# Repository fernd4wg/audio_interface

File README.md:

# Audio Interface

## Important Note
Make sure to always **git pull** before you start working.

This is being made on KiCAD 10. If you are using a different version and wish to make contributions there may be problems.

## Getting Started
To get this project on your computer, ensure you have git installed on your computer and in your terminal run:
```
git clone https://github.com/fernd4wg/audio_interface
```

After that, open up the *audio_interface.kicad_pro* file through KiCAD.

Done.

## 3D Models
I am going to use 3rd party 3D models for this project because KiCAD does not have all the necessary 3D models for this PCB.

I will provide a fork of my KiCAD 3D model directory that you can replace with yours if you so wish.

Additionally, I will provide a folder with the 3rd party 3D models I use for this project in this repository. ***Note** that those being here will not make them appear on the 3D model of the PCB. You will need to set that up yourself if you do not replace your KiCAD 3D model library with mine*

## Technical Details
If you are curious about the technical details of the audio interface I will eventually provide a documentation folder where a there will be a document that documents the technical side of the design.

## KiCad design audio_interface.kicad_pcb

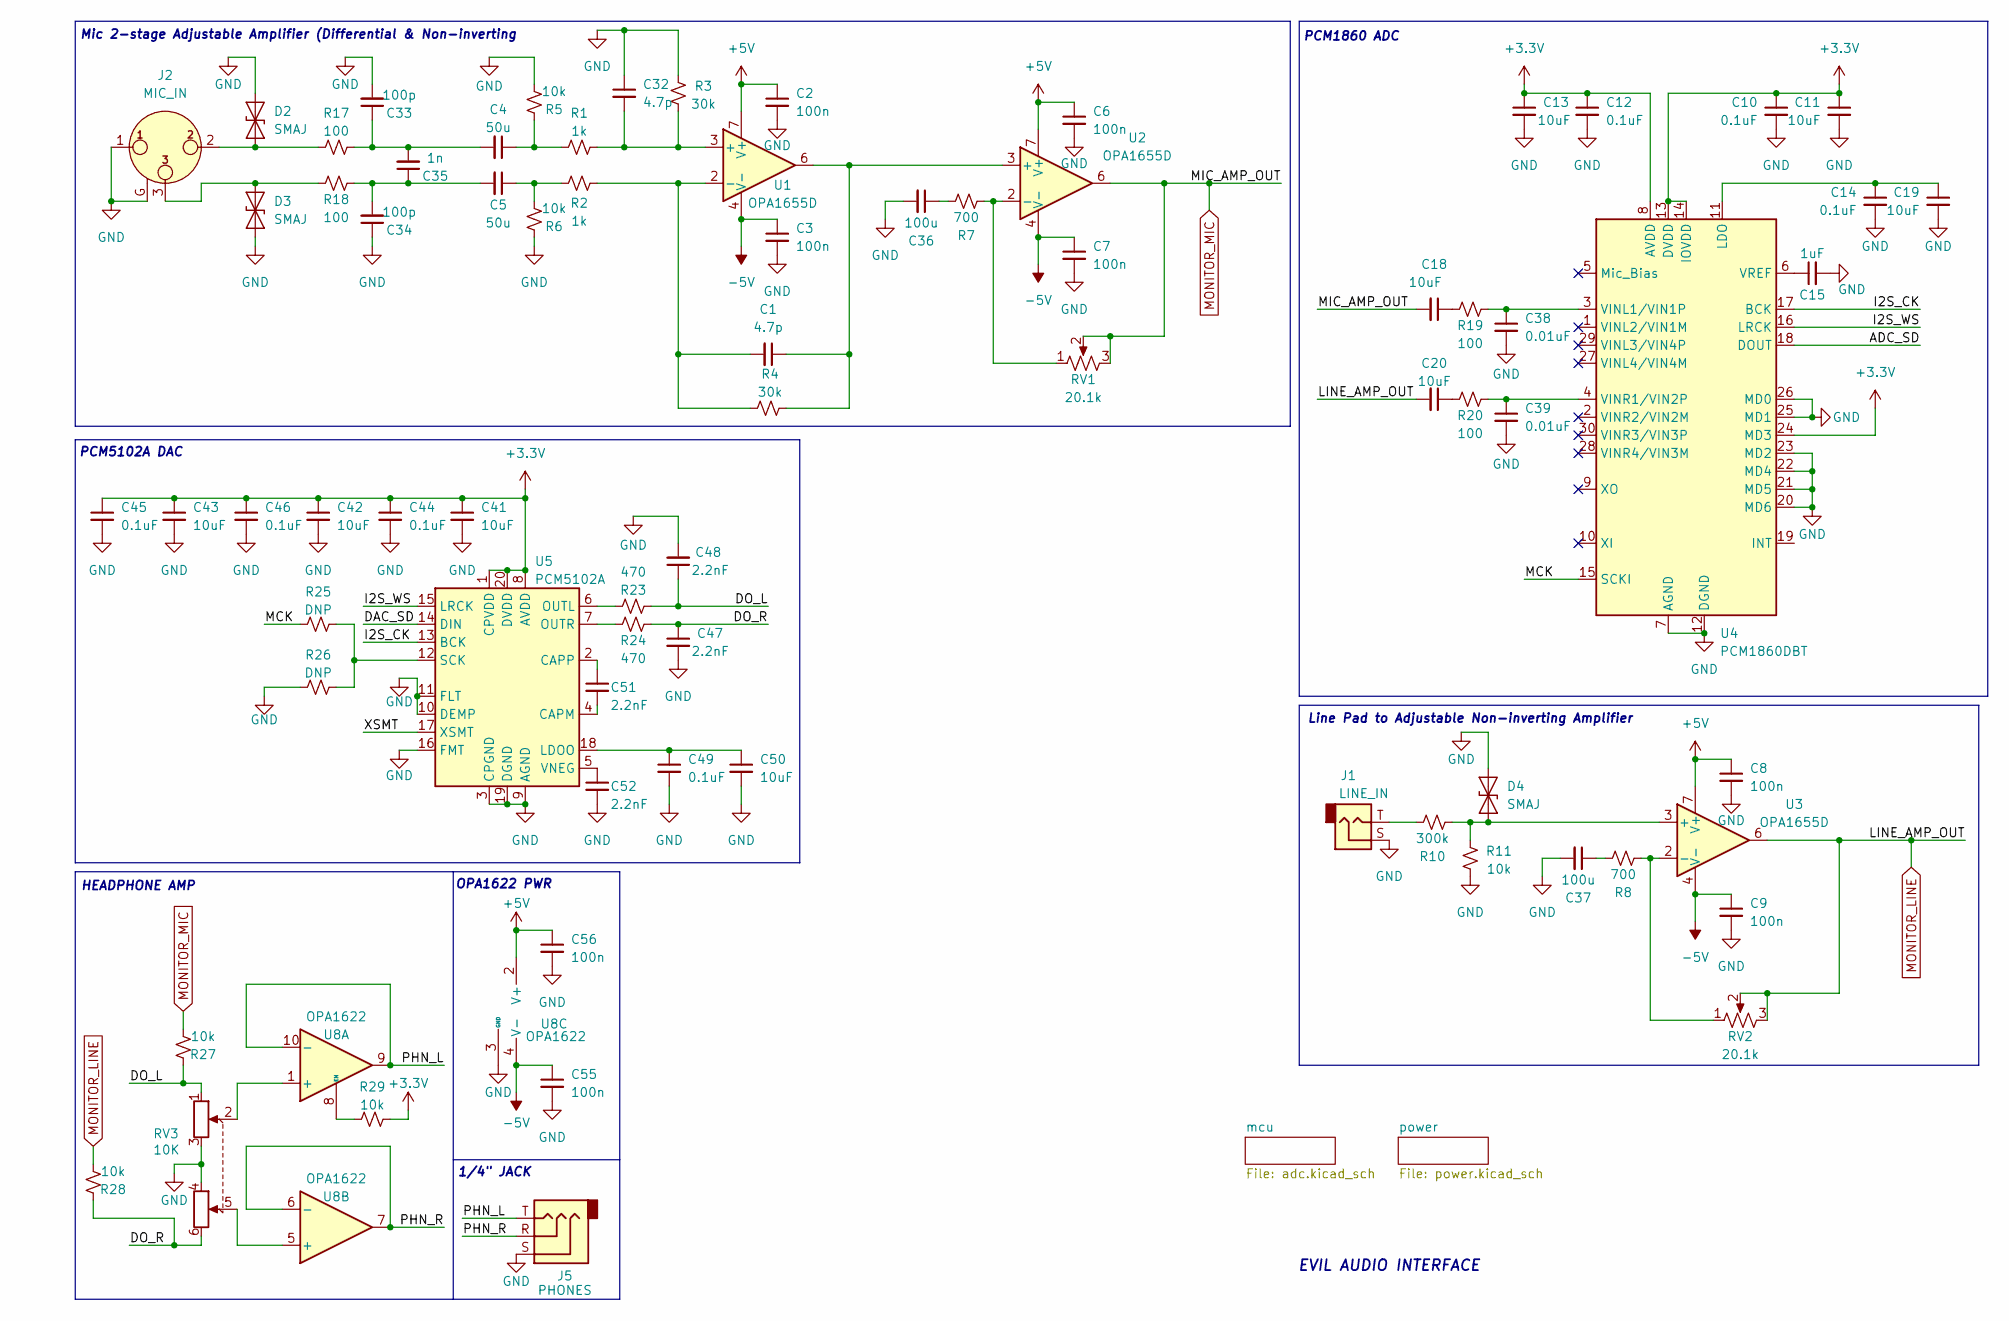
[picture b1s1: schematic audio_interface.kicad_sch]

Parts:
C1, C32: 4.7p; C_0805_2012Metric
C2, C3, C6, C7, C8, C9, C55, C56: 100n; C_0805_2012Metric
C4, C5: 50u; C_0805_2012Metric
C10, C12, C14, C44, C45, C46, C49: 0.1uF; C_0805_2012Metric
C11, C13, C18, C19, C20, C41, C42, C43, C50: 10uF; C_0805_2012Metric
C15: 1uF; C_0805_2012Metric
C33, C34: 100p; C_0805_2012Metric
C35: 1n; C_0805_2012Metric
C36, C37: 100u; C_0805_2012Metric
C38, C39: 0.01uF; C_0805_2012Metric
C47, C48, C51, C52: 2.2nF; C_0805_2012Metric
D2, D3, D4: SMAJ; D_SMA
J1: LINE_IN; Jack_6.35mm_Neutrik_NMJ4HCD2_Horizontal
J2: MIC_IN; Jack_XLR-6.35mm_Neutrik_NCJ6FI-H_Horizontal
J5: PHONES; Jack_6.35mm_Neutrik_NMJ4HCD2_Horizontal
R1, R2: 1k; R_0805_2012Metric
R3, R4: 30k; R_0805_2012Metric
R5, R6, R11, R27, R28, R29: 10k; R_0805_2012Metric
R7, R8: 700; R_0805_2012Metric
R10: 300k; R_0805_2012Metric
R17, R18, R19, R20: 100; R_0805_2012Metric
R23, R24: 470; R_0805_2012Metric
R25, R26: DNP; R_0805_2012Metric
RV1, RV2: 20.1k; Potentiometer_Alps_RK09K_Single_Horizontal
RV3: 10K; Potentiometer_Alps_RK097_Dual_Horizontal
U1, U2, U3: OPA1655D; SOIC-8_3.9x4.9mm_P1.27mm
U4: PCM1860DBT; TSSOP-30_4.4x7.8mm_P0.5mm
U5: PCM5102A; TSSOP-20_4.4x6.5mm_P0.65mm
U8: OPA1622; Texas_S-PVSON-N10

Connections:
+3.3V: C10.1, C11.1, C12.1, C13.1, C41.1, C42.1, C43.1, C44.1, C45.1, C46.1, R29.2, U4.8 (AVDD), U4.13 (DVDD), U4.14 (IOVDD), U4.24 (MD3), U5.1 (CPVDD), U5.8 (AVDD), U5.20 (DVDD); also elsewhere on the board
+5V: C2.1, C6.1, C8.1, C56.1, U1.7 (V+), U2.7 (V+), U3.7 (V+), U8.2 (V+)
-5V: C3.1, C7.1, C9.1, C55.1, U1.4 (V-), U2.4 (V-), U3.4 (V-), U8.4 (V-), U8.11 (V-)
/ADC_SD: U4.18 (DOUT)
/DAC_SD: U5.14 (DIN)
/DO_L: C48.1, R23.1, R27.2, RV3.1
/DO_R: C47.1, R24.2, R28.2, RV3.6
/I2S_CK: U4.17 (BCK), U5.13 (BCK)
/I2S_WS: U4.16 (LRCK), U5.15 (LRCK)
/MCK: R25.1, U4.15 (SCKI)
/PHN_L: J5.T, U8.9, U8.10 (-)
/PHN_R: J5.R, U8.6 (-), U8.7
/XSMT: U5.17 (XSMT)
GND: C2.2, C3.2, C6.2, C7.2, C8.2, C9.2, C10.2, C11.2, C12.2, C13.2, C14.2, C15.2, C19.2, C32.1, C33.2, C34.1, C36.2, C37.2, C38.2, C39.2, C41.2, C42.2, C43.2, C44.2, C45.2, C46.2, C47.2, C48.2, C49.2, C50.2, C52.2, C55.2, C56.2, D2.2 (A2), D3.1 (A1), D4.2 (A2), J1.S, J2.1, J2.G, J5.S, R3.2, R5.1, R6.2, R11.2, R26.1, RV3.3, RV3.4, U4.7 (AGND), U4.12 (DGND), U4.20 (MD6), U4.21 (MD5), U4.22 (MD4), U4.23 (MD2), U4.25 (MD1), U4.26 (MD0), U5.3 (CPGND), U5.9 (AGND), U5.10 (DEMP), U5.11 (FLT), U5.16 (FMT), U5.19 (DGND), U8.3 (GND); also elsewhere on the board
MONITOR_LINE: C20.2, R28.1, RV2.2, RV2.3, U3.6
MONITOR_MIC: C18.2, R27.1, RV1.2, RV1.3, U2.6
unnamed: C4.1, R1.1, R5.2
unnamed: C5.1, R2.1, R6.1
unnamed: C18.1, R19.1
unnamed: C20.1, R20.1
unnamed: C4.2, C33.1, C35.2, R17.2
unnamed: C5.2, C34.2, C35.1, R18.2
unnamed: C36.1, R7.1
unnamed: C37.1, R8.1
unnamed: D2.1 (A1), J2.2, R17.1
unnamed: D3.2 (A2), J2.3, R18.1
unnamed: D4.1 (A1), R10.1, R11.1, U3.3 (+)
unnamed: J1.T, R10.2
unnamed: R29.1, U8.8 (EN)
unnamed: C32.2, R1.2, R3.1, U1.3 (+)
unnamed: C1.2, R2.2, R4.1, U1.2 (-)
unnamed: C1.1, R4.2, U1.6, U2.3 (+)
unnamed: R7.2, RV1.1, U2.2 (-)
unnamed: R8.2, RV2.1, U3.2 (-)
unnamed: C14.1, C19.1, U4.11 (LDO)
unnamed: C38.1, R19.2, U4.3 (VINL1/VIN1P)
unnamed: C39.1, R20.2, U4.4 (VINR1/VIN2P)
unnamed: C15.1, U4.6 (VREF)
unnamed: C51.2, U5.4 (CAPM)
unnamed: C51.1, U5.2 (CAPP)
unnamed: C49.1, C50.1, U5.18 (LDOO)
unnamed: R23.2, U5.6 (OUTL)
unnamed: R24.1, U5.7 (OUTR)
unnamed: R25.2, R26.2, U5.12 (SCK)
unnamed: C52.1, U5.5 (VNEG)
unnamed: RV3.2, U8.1 (+)
unnamed: RV3.5, U8.5 (+)

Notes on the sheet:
OPA1622 PWR
HEADPHONE AMP
EVIL AUDIO INTERFACE
PCM1860 ADC
PCM5102A DAC
Line Pad to Adjustable Non-inverting Amplifier
Mic 2-stage Adjustable Amplifier (Differential & Non-inverting
1/4" JACK

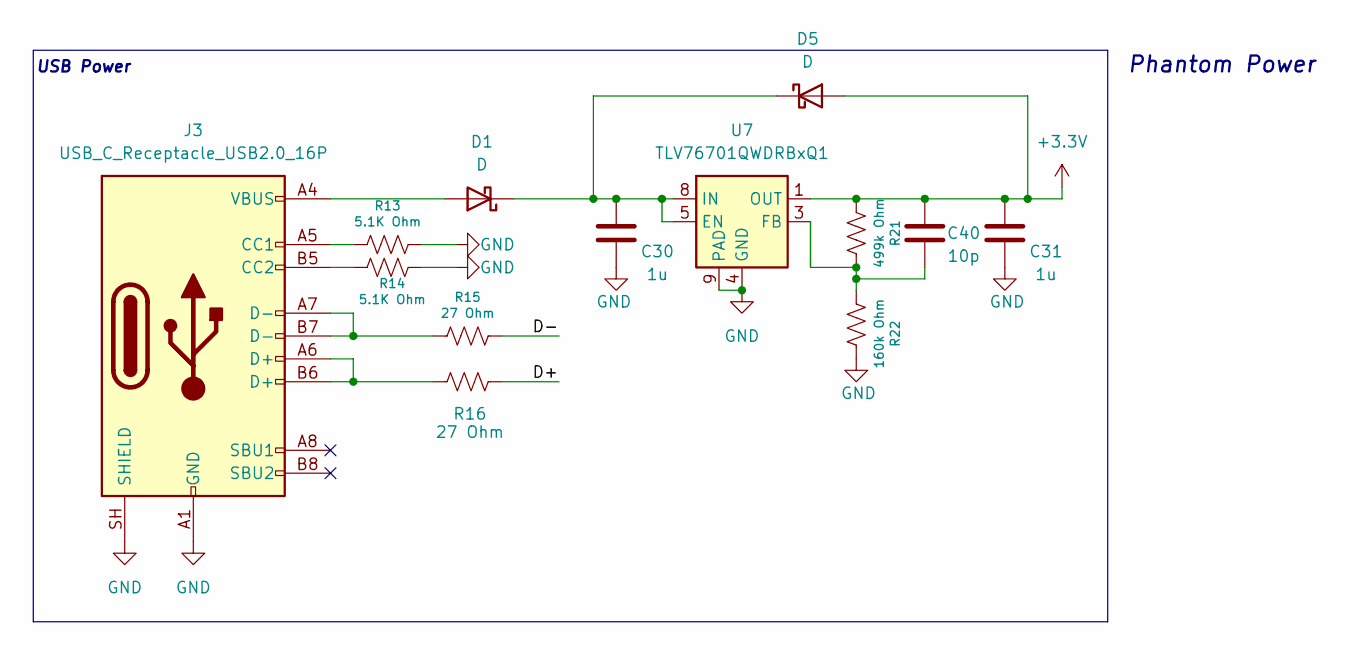
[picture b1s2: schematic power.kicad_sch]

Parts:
C30, C31: 1u; C_0603_1608Metric
C40: 10p; C_0603_1608Metric
D1, D5: D; D_SMA
J3: USB_C_Receptacle_USB2.0_16P; USB_C_Receptacle_HCTL_HC-TYPE-C-16P-01A
R13, R14: 5.1K Ohm; R_0402_1005Metric
R15, R16: 27 Ohm; R_0402_1005Metric
R21: 499k Ohm; R_0402_1005Metric
R22: 160k Ohm; R_0402_1005Metric
U7: TLV76701QWDRBxQ1; VSON-8-1EP_3x3mm_P0.65mm_EP1.65x2.4mm

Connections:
+3.3V: C31.1, C40.1, D5.2 (A), R21.1, U7.1 (OUT); also elsewhere on the board
/power/D+: R16.2
/power/D-: R15.2
GND: C30.2, C31.2, J3.A1 (GND), J3.A12 (GND), J3.B1 (GND), J3.B12 (GND), J3.SH (SHIELD), R13.2, R14.2, R22.2, U7.4 (GND), U7.6 (GND), U7.9 (PAD); also elsewhere on the board
unnamed: D1.2 (A), J3.A4 (VBUS), J3.A9 (VBUS), J3.B4 (VBUS), J3.B9 (VBUS)
unnamed: C30.1, D1.1 (K), D5.1 (K), U7.5 (EN), U7.8 (IN)
unnamed: J3.A5 (CC1), R13.1
unnamed: J3.B5 (CC2), R14.1
unnamed: J3.A6 (D+), J3.B6 (D+), R16.1
unnamed: J3.A7 (D-), J3.B7 (D-), R15.1
unnamed: C40.2, R21.2, R22.1, U7.3 (FB)

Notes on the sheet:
USB Power
Phantom Power

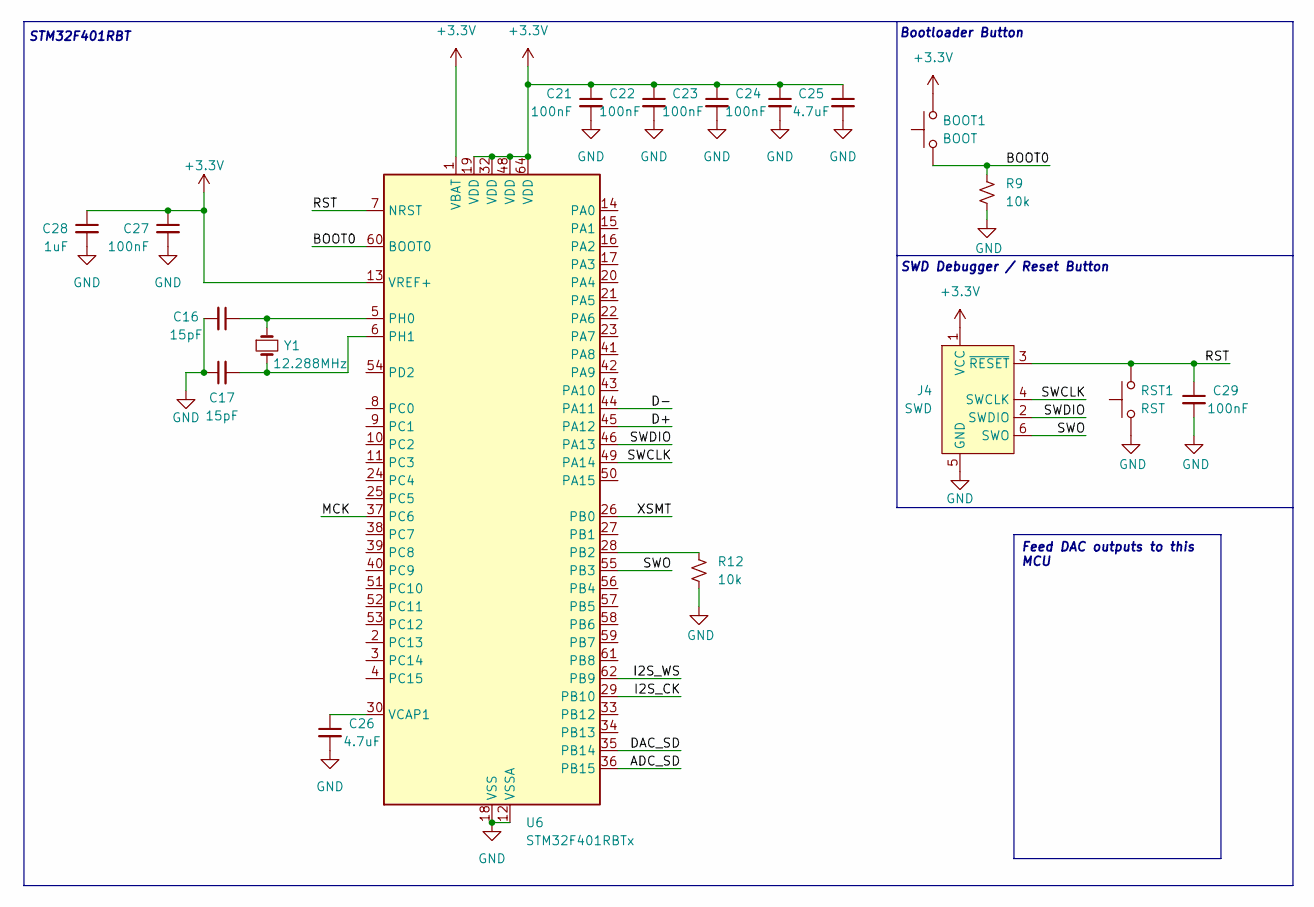
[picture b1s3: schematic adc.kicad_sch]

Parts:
BOOT1: BOOT
C16, C17: 15pF; C_0805_2012Metric
C21, C22, C23, C24, C27, C29: 100nF; C_0805_2012Metric
C25, C26: 4.7uF; C_0805_2012Metric
C28: 1uF; C_0805_2012Metric
J4: SWD; Tag-Connect_TC2030-IDC-NL_2x03_P1.27mm_Vertical
R9, R12: 10k; R_0805_2012Metric
RST1: RST
U6: STM32F401RBTx; LQFP-64_10x10mm_P0.5mm
Y1: 12.288MHz

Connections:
+3.3V: BOOT1.2, C21.1, C22.1, C23.1, C24.1, C25.1, C27.1, C28.1, J4.1 (VCC), U6.1 (VBAT), U6.13 (VREF+), U6.19 (VDD), U6.32 (VDD), U6.48 (VDD), U6.64 (VDD); also elsewhere on the board
/mcu/ADC_SD: U6.36 (PB15)
/mcu/BOOT0: BOOT1.1, R9.1, U6.60 (BOOT0)
/mcu/D+: U6.45 (PA12)
/mcu/D-: U6.44 (PA11)
/mcu/DAC_SD: U6.35 (PB14)
/mcu/I2S_CK: U6.29 (PB10)
/mcu/I2S_WS: U6.62 (PB9)
/mcu/MCK: U6.37 (PC6)
/mcu/RST: C29.1, J4.3 (~RESET), RST1.2, U6.7 (NRST)
/mcu/SWCLK: J4.4 (SWCLK), U6.49 (PA14)
/mcu/SWDIO: J4.2 (SWDIO), U6.46 (PA13)
/mcu/SWO: J4.6 (SWO), U6.55 (PB3)
/mcu/XSMT: U6.26 (PB0)
GND: C16.2, C17.1, C21.2, C22.2, C23.2, C24.2, C25.2, C26.2, C27.2, C28.2, C29.2, J4.5 (GND), R9.2, R12.2, RST1.1, U6.12 (VSSA), U6.18 (VSS), U6.31 (VSS), U6.47 (VSS), U6.63 (VSS); also elsewhere on the board
unnamed: R12.1, U6.28 (PB2)
unnamed: C16.1, U6.5 (PH0), Y1.1
unnamed: C17.2, U6.6 (PH1), Y1.2
unnamed: C26.1, U6.30 (VCAP1)

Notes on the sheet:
Bootloader Button
STM32F401RBT
SWD Debugger / Reset Button
Feed DAC outputs to this MCU

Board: 2 copper layers, 103 parts (0 on the bottom side), 59 nets, no tracks yet.
